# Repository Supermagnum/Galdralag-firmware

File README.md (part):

# Galdr — Galdralag Firmware

## Open Invention Network

This project is **registered with the [Open Invention Network (OIN)](https://openinventionnetwork.com/)**. OIN is a defensive patent pool: members cross-license Linux-related patents so participants can ship and use open-source software with reduced patent exposure.

Status: Waiting for:
https://github.com/betrusted-io/xous-core/pull/937

---

## Table of contents

- [Open Invention Network](#open-invention-network)
- [Security notice: Shamir host split](#security-notice-shamir-host-split-fixed-prior-shares-compromised)
- [What this is](#what-this-is)
  - [Galdra contact metadata](#galdra-contact-metadata)
  - [What this firmware is (and is not)](#what-this-firmware-is-and-is-not)
  - [Signed firmware (Ed25519, boot0)](#signed-firmware-ed25519-boot0)
- [Is this AI slop?](#is-this-ai-slop)
- [Test results](#test-results)
- [Why Rust?](#why-rust)
  - [Memory Safety](#memory-safety)
  - [System-level robustness (with limits)](#system-level-robustness-with-limits)
  - [Key material protection (project patterns)](#key-material-protection-project-patterns)
  - [Auditable by design](#auditable-by-design)
  - [What Rust does not prevent](#what-rust-does-not-prevent)
  - [Setting up a virtual machine for evaluation](#setting-up-a-virtual-machine-for-evaluation)
  - [Risk assessment and deployment](#risk-assessment-and-deployment)
- [Galdralag for dummies](#galdralag-for-dummies)
  - [What is GnuPG?](#what-is-gnupg)
- [GnuPG / OpenPGP keys and Galdra keys](#gnupg--openpgp-keys-and-galdra-keys)
  - [Metadata comparison (GnuPG vs Galdra)](#metadata-comparison-gnupg-vs-galdra)
- [Skipped and ignored tests](#skipped-and-ignored-tests)
- [About the name](#about-the-name)
- [Documentation](#documentation)
- [Code map (function and module index)](docs/CODE_MAP.md)
- [Crate dependencies (upstream vs project)](docs/CRATE_DEPENDENCIES.md)
- [Debugging instructions](docs/DEBUG_INSTRUCTIONS.md)
- [docs/AUDIT_LOG.md](docs/AUDIT_LOG.md)
- [docs/BIOMETRIC_API.md](docs/BIOMETRIC_API.md)
- [docs/HARDWARE_BRINGUP_TEST_PLAN.md](docs/HARDWARE_BRINGUP_TEST_PLAN.md)
- [docs/KEY_LIFECYCLE.md](docs/KEY_LIFECYCLE.md)
- [docs/RRAM_LAYOUT.md](docs/RRAM_LAYOUT.md)
- [docs/THREE_FACTOR_AUTH.md](docs/THREE_FACTOR_AUTH.md)
- [docs/THREAT_MODEL.md](docs/THREAT_MODEL.md)
- [Glossary (plain language)](docs/GLOSSARY.md)
- [OpenPGP and GnuPG compatibility](#openpgp-and-gnupg-compatibility)
- [Token session and key export](#token-session-and-key-export)
- [Web of Trust and Key Signing Parties](#web-of-trust-and-key-signing-parties)
  - [Obtaining your Galdralag fingerprint](#obtaining-your-galdralag-fingerprint)
  - [What is the web of trust?](#what-is-the-web-of-trust)
  - [How it works](#how-it-works)
  - [Key signing parties](#key-signing-parties)
  - [Typical workflow at a key signing party](#typical-workflow-at-a-key-signing-party)
  - [Fingerprints instead of full keys at the event](#fingerprints-instead-of-full-keys-at-the-event)
  - [Keyservers](#keyservers)
  - [Using keyservers](#using-keyservers)
  - [Common keyservers](#common-keyservers)
  - [Best practices and caveats](#best-practices-and-caveats)
  - [Fulla (WoT registry server)](https://github.com/Supermagnum/Fulla)
- [Standards vs. firmware-specific features](#standards-vs-firmware-specific-features)
- [Shamir secret sharing and drive encryption](#shamir-secret-sharing-and-drive-encryption)
- [German eID and Governikus as a trust anchor for public keys](#german-eid-and-governikus-as-a-trust-anchor-for-public-keys)
- [Standards process: Shamir and ephemeral key exchange](#standards-process-shamir-and-ephemeral-key-exchange)
  - [CESS (related open standard)](#cess-related-open-standard)
- [Sequoia PGP (if this repository is unresponsive)](#sequoia-pgp-if-this-repository-is-unresponsive)
- [Platform support (Linux only)](#platform-support-linux-only)
- [Build, install, and uninstall](#build-install-and-uninstall)
  - [Compile firmware](#compile-firmware)
  - [Flashing](#flashing)
  - [Compile and install host tools (`galdra`, `galdrad`, `galdra-gtk`)](#compile-and-install-host-tools-galdra-galdrad-galdra-gtk)
  - [Run `galdrad` and the desktop GUI (`galdra-gtk`)](#run-galdrad-and-the-desktop-gui-galdra-gtk)
  - [Uninstall host tools](#uninstall-host-tools)
- [Key capabilities](#key-capabilities)
  - [What makes this token unusual](#what-makes-this-token-unusual)
  - [Dual-hardware-key quorum (integrator pattern)](#dual-hardware-key-quorum-integrator-pattern)
  - [Cryptographic capabilities](#cryptographic-capabilities)
    - [Asymmetric / key agreement](#asymmetric--key-agreement)
    - [Symmetric / AEAD](#symmetric--aead)
    - [Key derivation / MAC / digest](#key-derivation--mac--digest)
    - [Key management](#key-management)
  - [Security properties](#security-properties)
  - [PIN policy](#pin-policy)
- [Post-quantum status](#post-quantum-status)
  - [Implemented — unaudited crate (feature-gated)](#implemented--unaudited-crate-feature-gated)
  - [Pending independent audit — not yet implemented](#pending-independent-audit--not-yet-implemented)
  - [Will not be implemented](#will-not-be-implemented)
- [Zeroisation — hardware caveat](#zeroisation--hardware-caveat)
- [Workspace layout](#workspace-layout)
- [Cryptographic dependency policy](#cryptographic-dependency-policy)
- [Quick start](#quick-start)
- [Known limitations / open work](#known-limitations--open-work)
  - [CCID initial PIN: Dabao CCID vs legacy CDC](#ccid-initial-pin-dabao-ccid-vs-legacy-cdc)
- [License](#license)

---

## What this is

Firmware for **Baochip-1x** (Dabao evaluation board) devices running the
**[Xous](https://github.com/betrusted-io/xous-core)** microkernel, built
for `riscv32imac-unknown-none-elf`.

It's located here:
https://www.baochip.com/

The device is a hardware security token in the same category as
Nitrokey-class devices, with OpenPGP smartcard-class behaviour and an
encrypted vault. The full hardware stack — RTL, schematics, bootloader,
OS — is open source and auditable.

Hardware specification, boot model, requirement tables, and ComboHash/PKE
usage are documented in **[Supermagnum/Baochip-1x-firmware](https://github.com/Supermagnum/Baochip-1x-firmware)**.
The **Dabao** evaluation board (KiCad, schematics, switches, pinout) is **[baochip/dabao](https://github.com/baochip/dabao)**. To enter **bootloader mode** for flashing, **press SW2** to toggle it (see that repo's schematic).
Architecture notes for this repository: [docs/ARCHITECTURE.md](docs/ARCHITECTURE.md).

### Galdra contact metadata

The **Galdra** host tool keeps a **local SQLite** directory of recipients (contacts). Each stored identity includes public key material plus optional **sidecar labels** (see the table below). These tags live in the host database and, for **Galdra keys**, in the on-chip **contact store** (`crates/contact-store`). They are **not** magically bound to OpenPGP User IDs unless you align them yourself, and they are **not** cryptographically asserted unless you check them **out of band**. Optional **`galdra keyserver push`** can send overlapping fields to a project registry as JSON alongside the exported public key. Per-field provenance on the token uses **SelfAttested**, **HostVerified**, **RegistrySync**, and **OobVerified** (see [Metadata comparison (GnuPG vs Galdra)](#metadata-comparison-gnupg-vs-galdra) and the contact-store layout in [docs/RRAM_LAYOUT.md](docs/RRAM_LAYOUT.md)).

| Field | Purpose | Host (`galdra` SQLite) | On-chip contact store | Format / limit |
|-------|---------|--------------------------|------------------------|----------------|
| **Contact id** | Stable host primary key | Yes | No | Text (`id` in SQLite) |
| **Display name** | Human-readable label | Yes | Yes | UTF-8 string; **240 bytes** max per heap field on chip |
| **E-mail** | Primary mail address | Yes | Yes | UTF-8 string; lookup on chip by e-mail scan |
| **Callsign** | Amateur-radio callsign | Yes | Yes | **12 bytes**, NUL-padded; lookup on chip |
| **DMR subscriber ID** | DMR radio ID | Yes | Yes | **32-bit** unsigned (`0` = absent); lookup on chip |
| **Badge number** | Employee or badge ID | Yes | Yes | UTF-8 string |
| **Organisation** | Agency or employer | Yes | Yes | UTF-8 string |
| **Department** | Team or unit | Yes | Yes | UTF-8 string |
| **Role** | Job or function label | Yes | Yes | UTF-8 string |
| **Note** | Free-form comment | Yes | Yes | UTF-8 string |
| **Radio affiliation** | Club, net, or alliance label | Yes | Yes | UTF-8 string |
| **Street** | Street address line | Yes | Yes | UTF-8 string |
| **Country** | Country name or code | Yes | Yes | UTF-8 string |
| **Postal code** | ZIP or postal code | Yes | Yes | UTF-8 string |
| **Region** | State, county, or region | Yes | Yes | UTF-8 string |
| **Fluxer ID** | Fluxer handle or id | Yes | Yes | UTF-8 string |
| **Discord ID** | Discord user id | Yes | Yes | UTF-8 string |
| **IRC id** | IRC nick or similar | Yes | Yes | UTF-8 string |
| **Phone number** | Voice or SMS contact number | Yes | No | UTF-8 string; **32** characters max on host; submitter-declared, not verified |
| **Fingerprint** | Key anchor (lookup, sync) | Yes (`pgp_fingerprint`) | Yes | **32 bytes**; OpenPGP v4 style on wire; **not** the same as a **`G:`** device fingerprint |
| **Public key** | Encryption / verify material | Yes (`pgp_pubkey`) | Yes (key region) | Algorithm: Ed25519, X25519, Brainpool P-256/P-384/P-512, NIST P-256/P-384, RSA-2048/3072/4096; up to **768 bytes** blob on chip |
| **PIN-protected key** | Key requires PIN unlock | Host stores OpenPGP keys separately | Yes | PIN verifier digest + AES-GCM wrap metadata on chip |
| **Last fetched** | When key material was refreshed | Yes (`fetched_at`) | Yes (`last_fetched`) | UTC on host; **32-bit** timestamp on chip |
| **Expires at** | Key expiry time | Yes | No | UTC datetime in SQLite only |
| **Key source** | How the host record was created | Yes (`source`) | No | e.g. manual, keyserver, WKD, LDAP, file, peer |
| **Field provenance** | Trust label per metadata field | No | Yes (`source_map`) | Two bits per field: SelfAttested, HostVerified, RegistrySync, OobVerified |
| **Record flags** | Active, stale, own-identity, revoked | Partially (host logic) | Yes | e.g. **STALE**, **SELF_KEY** on chip |

Host-side details and CLI behaviour: [docs/GALDRA-TOOL.md](docs/GALDRA-TOOL.md). Wire layout and slot counts: `crates/contact-store/src/layout.rs` and [docs/RRAM_LAYOUT.md](docs/RRAM_LAYOUT.md).

### What this firmware is (and is not)

**This firmware is** a **hardware security token** for **Baochip-1x**: an **OpenPGP card application** over **USB CCID**, with an on-device **vault**, **PIN policy**, and repository-specific features (**cipher profiles** — you can **stack** **up to four** different symmetric ciphers in one cascade, each with its own derived key; see [Key capabilities](#key-capabilities)), Shamir-related flows, authenticated ephemeral ECDH where implemented, and **Galdra** host tools). The primary interoperability target is **GnuPG-style** OpenPGP card usage, not every token protocol on the market.

**This firmware is not:**

- **FIDO2 / CTAP2 / WebAuthn** — different standards; no CTAP **user-presence** button model and no planned CTAP stack. Use a FIDO security key if you need WebAuthn. (See also [OpenPGP and GnuPG compatibility](#openpgp-and-gnupg-compatibility) and the standards table under [Standards vs. firmware-specific features](#standards-vs-firmware-specific-features).)
- **TOTP / HOTP (OATH one-time passwords)** — those protocols expect a **real-time clock** (TOTP) or an OATH-oriented counter workflow and UX; this device is **not** built as a dedicated OTP token.
- **USB HID keyboard "password typer"** — there is no USB keyboard personality to inject keystrokes into the host. Planned credential storage (see [docs/future-todo.md](docs/future-todo.md)) is described as retrieval through **authenticated host tooling**, not HID typing.
- **A general multi-applet Java Card platform** — scope is this **Galdr** firmware and its documented surfaces, not arbitrary third-party smart-card applets.

Crate-level exclusions aligned with the same constraints are listed under **[Crates Explicitly Excluded](docs/future-todo.md#crates-explicitly-excluded)** in [docs/future-todo.md](docs/future-todo.md).

**CESS:** This firmware **conforms to CESS** for the normative constructions implemented in-tree (including **Mode A** outer AEAD, **HKDF-BLAKE3** for **`K_outer`**, and byte-wise GF(2^8) Shamir splitting). The full alignment statement, deviation register, and **certification level** (for example **CESS-CORE** for the full fixed layer) are documented in [docs/CESS_CONFORMANCE.md](docs/CESS_CONFORMANCE.md) and [CESS (related open standard)](#cess-related-open-standard) below.

The **OpenPGP / CCID** application logic is in **`crates/usb-personality`**. On **Xous**, the USB service that exposes CCID is **`usb-bao1x`** (in your **xous-core** checkout), built with feature **`ccid-openpgp`**, using **`crates/baochip-openpgp`** for the OpenPGP RRAM window and provisioning. Layout: [docs/RRAM_LAYOUT.md](docs/RRAM_LAYOUT.md). Pre-production gaps (operator PIN UX, platform map sign-off): [Known limitations / open work](#known-limitations--open-work).

The overall goal remains a complete, tested, open-source hardware security token firmware: **OpenPGP card–style behaviour** for GnuPG over CCID (see [OpenPGP and GnuPG compatibility](#openpgp-and-gnupg-compatibility)), plus **additional on-device features** not currently defined by the OpenPGP card standard — ephemeral ECDH with forward secrecy, Shamir K-of-N, cipher-agnostic profiles, microSD decoy volume — as summarised in [Standards vs. firmware-specific features](#standards-vs-firmware-specific-features). All on open RTL with a reproducible bootloader.

For deployments that need **two separate physical tokens** (or **K-of-N** share-holders) before unlocking servers, firewalls, medicine vaults, or encrypted volumes, see [Dual-hardware-key quorum (integrator pattern)](#dual-hardware-key-quorum-integrator-pattern) under [Key capabilities](#key-capabilities). Each device is **one** credential source; quorum enforcement is **your** access gateway, PAM layer, or panel — not this firmware.

### Signed firmware (Ed25519, boot0)

Shippable firmware for **Baochip-1x** is **signed** with **Ed25519**. You sign the firmware image with an **Ed25519** private key; **GnuPG** can do this with **`gpg --sign`** using an **Ed25519 signing subkey** (the usual OpenPGP detached-signature workflow, adapted to whatever packaging your build emits). The immutable **boot0** ROM in the SoC **verifies** that signature against the **corresponding public keys burned into the device** (and the wider **key manifest** for the boot chain) **before** the next stage — **boot1** — is allowed to run. **boot1** then loads signed application images (for example **UF2** blobs delivered over USB mass storage in bootloader mode). Default parts carry **four** on-chip Ed25519 public keys (roles such as code deployment, beta, and developer); **boot0** / **boot1** enforce a **mutual-distrust** policy between Baochip and third-party signing keys. Full boot flow, **UF2** delivery, console, **boot1** updates, and security model: **[Getting Started with Baochip Targets](https://github.com/betrusted-io/xous-core/blob/dev/README-baochip.md)** in **xous-core**.

## Skipped and ignored tests

Not every test runs in every command; that is intentional.

- **`xtask` not in the default workspace test:** The common recipe is `cargo test --workspace --exclude xtask` because `xtask` is a build-orchestration crate. Run `cargo test -p xtask` when you want its tests.
- **Tests marked `#[ignore]`:** These are skipped unless you pass `--ignored` (and any needed crate filters). Reasons include: coverage that is already exercised in focused unit tests (e.g. post-drop zeroization), **slow** cases (e.g. RSA key generation), and **hardware or token-dependent** flows in host tools such as `galdra` that need a connected device or fixtures.
- **`test-all --no-fuzz`:** Skips the **cargo-fuzz** step to keep CI or quick runs short and to avoid requiring a nightly toolchain for that step; run `cargo run -p xtask -- test-all` without `--no-fuzz`, or invoke fuzz targets separately (see [`fuzz/README.md`](fuzz/README.md)).
- **`test-all --no-dudect`:** Skips the **dudect** timing suite (~15–20 minutes). CI uses this flag (shared runners are too noisy for a hard gate). Run `cargo run -p xtask -- timing-test` or `test-all` without `--no-dudect` locally.
- **Conformance vector suites:** Some groups are not executed (for example certain AES-GCM Wycheproof cases); see [`docs/TEST_RESULTS.md`](docs/TEST_RESULTS.md) for what is in scope.

One can also check integrity of crates with this when the pr is closed:
https://github.com/rust-lang/cargo/issues/16850

> **Status:** Ready for testing by humans, on real hardware — no production-ready release exists.
> It's written in Rust using validated and audited crypto crates. 
> Cryptographic primitives are drawn exclusively from audited workspace
> dependencies. Post-quantum algorithms are feature-gated and marked
> **PENDING INDEPENDENT AUDIT**. See [Post-quantum status](#post-quantum-status).

> **Note:** Parts of this project were developed with AI assistance (Claude, Anthropic).
> The design, cryptographic choices, and security decisions have not been reviewed
> by a professional cryptographer. Treat this as an experimental project and apply
> your own critical judgement. Independent expert review is strongly recommended
> before any production deployment.

It is ready for testing by humans. **You** decide whether to build or run any of this software; there may be bugs that **unit tests, fuzzing, and other checks** have not found. Using an **optional virtual machine** for experimentation **reduces risk** to your host system but does not eliminate it. Detailed results are in **[Test results](#test-results)** ([`docs/TEST_RESULTS.md#run-metadata`](docs/TEST_RESULTS.md#run-metadata)). **Plain-language definitions** (A–Z) of technical terms: **[Glossary](docs/GLOSSARY.md)**.

## Is this AI slop?

The primary developer has a **neurological condition related to dyscalculia**. Dyscalculia affects number sense and related symbolic processing in ways that, for them, make **traditional programming** — hand-authored code editing as the sole workflow — **not workable** without assisted tooling (for example conversational AI editors). That constraint is distinct from correctness: reviewers should still weigh tests, fuzzing, and independent audit as documented elsewhere on this page.

A cryptographer or serious implementer reviewing Galdralag will typically open `crates/vault/tests/` and `crates/cipher-profile/tests/` before reading prose. The test suite is the proof of work: it encodes domain knowledge that cannot be substituted with narrative alone.

That is not a reason to hide the point from everyone else. People evaluating the project for procurement, deciding whether to contribute, or shipping code without deep training in cryptographic testing methodology still deserve a pointer to the concrete evidence. 

**What to look at:** Conformance material includes RFC 8439 worked examples for ChaCha20-Poly1305 under `crates/vault/tests/rfc_vectors/`, vendored Wycheproof JSON for ChaCha20-Poly1305 and Brainpool ECDH/ECDSA edge cases under `crates/vault/tests/data/wycheproof/`, BSI TR-03111 vectors for BrainpoolP256r1 and P384r1 under `crates/vault/tests/bsi_vectors/`, official BLAKE3 reference vectors (all 35 input lengths, all three modes) under `crates/vault/tests/blake3_vectors.json`, Twofish specification vectors (1203 cases including Monte Carlo) under `crates/vault/tests/twofish_vectors.json`, and the project's own CESS cascade KAT fixture with independently verified intermediates under `crates/cipher-profile/tests/fixtures/cascade_cess_kat.json`. Together these are the ground truth the runner and reviewers can exercise with `cargo test --workspace` and `python3 scripts/verify_cascade_kats.py`.

**RFC 8439** is published by the Internet Engineering Task Force (IETF), the organisation that standardises much of how the internet interoperates. RFCs (Request for Comments) are the usual form for protocol and many cryptographic specifications. RFC 8439 defines ChaCha20-Poly1305 authenticated encryption (building on Daniel Bernstein's designs) and includes concrete worked examples with specific inputs and expected outputs so independent implementations can check they match the standard byte-for-byte. The widely reproduced plaintext beginning with *Ladies and Gentlemen of the class of '99: wear sunscreen* appears in the RFC's appendix examples: if your code reproduces the AEAD output exactly, you have a strong check that you implemented the construction correctly. It is the cryptographic analogue of an official answer key. ChaCha20-Poly1305 is the inner layer of every multi-layer cascade profile in this firmware, so this check sits at the foundation of the entire cipher stack.

**Wycheproof** is a test corpus released by Google's security team (2017). The name refers to Mount Wycheproof in Australia — often cited as the world's smallest mountain — because the project focuses on clearing small but fatal hurdles: integer overflows, boundary cases, malformed inputs, and tampered authentication tags; failures that show up repeatedly in real deployed crypto. It complements RFC-style vectors: RFC 8439-style examples demonstrate correctness against the published AEAD; Wycheproof stresses robustness where implementations historically break. In this repository Wycheproof JSON covers ChaCha20-Poly1305, AES-GCM, HMAC, HKDF, X25519, Ed25519, RSA, and Brainpool ECDH/ECDSA variants.

**BSI TR-03111** is the technical guideline for elliptic curve cryptography published by the German Federal Office for Information Security (Bundesamt fur Sicherheit in der Informationstechnik). Version 2.10 is the current revision. The Brainpool curves used in this firmware — P256r1 and P384r1 — are specified in BSI standards, making TR-03111 the natural reference for their test vectors. Each curve has ECDH and ECDSA coverage; ECDSA signatures were additionally cross-checked against an independent Python implementation using the `cryptography` library.

**BLAKE3 reference vectors** are the official test corpus published alongside the BLAKE3 specification by its authors. They cover 35 input lengths from 0 to 102400 bytes, specifically chosen to exercise all internal chunk and tree-hashing boundary conditions that are invisible to short-input tests. All three BLAKE3 modes — default hash, keyed hash, and derive-key — are covered. BLAKE3 is used throughout this firmware for HKDF key derivation and inter-layer integrity checks in the cascade cipher profiles; the boundary coverage matters because BLAKE3's tree construction only activates above 1024 bytes.

**The test suite is also tamper detection for the supply chain.** All cryptographic primitives in this firmware come from audited RustCrypto crates — no cryptography is implemented in-tree. Because the conformance vectors above are run against those crates on every `cargo test --workspace`, any dependency that has been tampered with or substituted will produce a known-answer test failure before the compromised code reaches a deployed system. `python3 scripts/verify_cascade_kats.py` adds a second independent path: a Python implementation checks the same intermediate values in the cascade KAT fixture, so even a compromised Rust toolchain producing wrong output is caught by the cross-check. This is a meaningfully stronger supply chain integrity story than binding to a C library, where equivalent verification of every internal operation requires significantly more effort and specialist tooling.

It is now up to the reader to judge whether these claims are false or not.

## Galdralag for dummies

You plug it into a USB port. From the host's perspective the firmware can present **crypto mode** or **camouflage mode**. In crypto mode your computer sees a smart card: you use **GnuPG** or a compatible OpenPGP stack ([What is GnuPG?](#what-is-gnupg)) the same way you would any other hardware security token — the token handles the sensitive cryptographic operations so your private keys never exist unprotected on your computer. In camouflage mode it can enumerate as ordinary removable storage with innocuous-looking files so a quick look does not reveal its real role; see **Storage camouflage** below.

### What is GnuPG?

**GnuPG** stands for **GNU Privacy Guard**. It is the GNU project's implementation of **OpenPGP**, the open standard for key management and cryptographically protected messages (the same conceptual family as PGP, but specified in documents such as RFC 4880 and community updates). You normally run it as the **`gpg`** command on Linux, BSD, macOS, or Windows; many graphical mail and key utilities wrap this underneath.

People use GnuPG to:

- **Encrypt and decrypt** files or backups so only chosen recipients can read them.
- **Sign data** so others can check authenticity and integrity — common for software releases, distribution mirrors, and personal documents.
- **Protect email** end-to-end when paired with a suitable mail client (GnuPG handles the cryptography; the message format on the wire is OpenPGP).
- **Authenticate**, notably **SSH** logins when **`gpg-agent`** exposes authentication keys from a smart card or local keystore.
- **Lock and unlock an encrypted hard drive.** Linux can scramble a whole drive so it is unreadable without the right key. GnuPG can hold that key on your token, so the drive only opens when the token is plugged in.

**GnuPG and encrypted drives (LUKS).** Linux has a built-in way to encrypt an entire drive or partition, called **LUKS**. Once a drive is encrypted, it looks like meaningless noise to anyone without the key, so a lost or stolen laptop does not hand over your files.

Normally you unlock such a drive by typing a password. GnuPG lets you use your token instead. The idea is simple: the drive's unlock key is itself locked with your token's key. When you want to open the drive, the token unscrambles that unlock key for you, but only while the token is plugged in and you have entered your **PIN**. Pull the token out, and the drive cannot be opened at all, even on the same computer.

In short, this turns the token into a physical key for your encrypted drive. Setting it up (and adding a backup way in, in case the token is ever lost) is done with Linux's own disk tools; the token simply holds the key. If you would rather share the ability to unlock a drive among several people, so that no one person can do it alone, see [Shamir secret sharing and drive encryption](#shamir-secret-sharing-and-drive-encryption).

By default GnuPG stores keys under **`~/.gnupg`**. With an **OpenPGP smart card**, sensitive **private** keys live on the card; **`scdaemon`** (part of the GnuPG suite) talks **CCID**/**USB** to the card while **`gpg`** still assembles OpenPGP packets on the host.

**What you can use it for.** In **crypto mode** the token is meant for the same work as other OpenPGP smart cards: **signing and decrypting** mail and files, **authenticating** (for example SSH when you use `gpg-agent` as usual), and keeping **long-term private keys** off the machine you type on. Organisations can combine that with **Shamir shares** on the token so no single person holds the entire secret (described further below). **GnuPG** is the primary interoperability target on the host: this firmware implements the **OpenPGP card application** over **CCID**, which `scdaemon` drives (`gpg --card-status`, `gpg --card-edit`, and normal encrypt/sign/decrypt with keys on the card). Other software that speaks the same smart-card protocols may work too; commands, slots, algorithms, and current integration limits are in [OpenPGP and GnuPG compatibility](#openpgp-and-gnupg-compatibility). When **NFC** is brought up on the hardware (**planned** integration — **not** in firmware yet), the same device class can support **physical access**: tapping an NFC reader at a **door, gate, or lock panel** can take part in a policy that only releases the lock after cryptographic checks (often combined with PIN, biometrics, or Shamir-style quorum depending on the deployment). The PN532-oriented sketch for readers and panels is in [docs/NFC_PN532_INTEGRATION.md](docs/NFC_PN532_INTEGRATION.md).

That is the short version. Here is what makes it different from other tokens you may have encountered.

**Storage camouflage.** The device can act as ordinary removable storage so its real role is not obvious from a quick look. When you plug it into a typical computer, it can show up like a normal USB drive or SD-backed volume; you can fill the visible filesystem with plausible everyday files (for example vacation photos) so casual browsing reinforces the impression that it is only storage. That frustrates superficial inspection at a desk or checkpoint. Figuring out that it is actually a security token usually means taking the housing apart, not just plugging it in.

**Your keys stay on the device.** When you sign an email or decrypt a file, the private key never leaves the token. The computer sends the data in, the token does the work, the result comes back out. An attacker who compromises your computer gets nothing useful.

**Past sessions stay safe even if the token is stolen.** Most hardware tokens use a long-term private key directly for key agreement. This one generates a fresh throwaway key pair for every session, signs it with the long-term key to prove it is genuine, and then uses the throwaway pair for the actual exchange. If someone steals the token years from now and somehow extracts the long-term key, they still cannot decrypt anything from past sessions. This property is called forward secrecy, and it is unusual in hardware tokens.

**You can split the key between multiple people.** The token can divide the long-term key into N shares so that any K of those shares are needed to reconstruct it — but no single share holder can do anything alone. This is called Shamir secret sharing. It is useful for organisational keys where no single person should have unilateral access, or as a backup strategy where shares are stored in separate locations. This is also unusual in hardware tokens.

**The encryption is layered.** Rather than encrypting your data with a single cipher, the token can run it through multiple independent ciphers in sequence — for example ChaCha20, then Serpent, then Twofish — each using a separately derived key. A future breakthrough that breaks one cipher does not break the others. The specific combination is called a cipher profile, and you can choose from several built-in ones depending on how much caution your situation requires.

My personal recommendation is **BrainpoolP256r1 + ChaCha20-Poly1305 + BLAKE3**. This is the built-in `standard` profile. It uses the BSI Brainpool P-256 curve for ephemeral key agreement, ChaCha20-Poly1305 for symmetric encryption, and BLAKE3 for key derivation and inter-layer integrity. It is fast, well-tested, battery friendly (ChaCha20-Poly1305 was designed to be efficient on hardware without AES acceleration, reducing CPU time and host power draw; P-256 is the smallest of the three Brainpool curves in this firmware), and does not depend on any NIST-designed primitive. If you need a higher margin against a future cryptanalytic break against a single cipher, the `conservative` profile adds a Serpent-256 layer on top.

**The algorithm choices are deliberate.** The ciphers used — ChaCha20-Poly1305, Serpent, Twofish, Camellia — were all designed independently of government standards bodies. AES and the NIST suite are intentionally excluded. This is a conscious choice for users and organisations who want cryptographic independence from any single country's standards process. Camellia was evaluated independently by the EU NESSIE project and Japan's CRYPTREC programme, and is specified in RFC 3713 and ISO/IEC 18033-3.

**A wrong PIN locks you out properly.** The token counts failed PIN attempts before it checks whether the PIN is correct, not after. This means a crash or power loss mid-attempt cannot be exploited to reset the counter. After too many wrong attempts the token zeroises sensitive material.

**What it does not do yet.** There is no hardware available yet — this is firmware under active development. End-to-end testing with real USB hardware and GnuPG is a future milestone. **NFC** transport and **door-style access readers** are described in the documentation as **integration targets**, not shipped behaviour yet. The biometric third factor described in the documentation is not yet implemented. Some timing side-channel tests that require real hardware cannot be completed until a device exists.

---

## GnuPG / OpenPGP keys and Galdra keys

Galdralag can work with two different kinds of asymmetric key at once. They answer different questions on the device and on the host, and they are not interchangeable even when they belong to the same person. The sections **OpenPGP and GnuPG compatibility**, **Web of Trust and Key Signing Parties**, [Galdra contact metadata](#galdra-contact-metadata), and [Metadata comparison (GnuPG vs Galdra)](#metadata-comparison-gnupg-vs-galdra) describe each stack in more detail; here is how they differ in everyday terms.

An **OpenPGP key**, in the sense GnuPG generates and uses, is a structured packet, not a bare public number. It bundles the primary key, subkeys for signing and encryption, and one or more **User IDs** — usually a display name and an email address such as `Alice Example <alice@example.org>`. Other people can sign those User IDs to say they believe the identity claim is genuine; that social graph is the basis of the web of trust described in **Web of Trust and Key Signing Parties** later in this README. When Galdralag acts as an OpenPGP smartcard, it holds the **private** key material on chip and performs signing and decryption there. The **public** key, the User IDs, and the signatures from others live on the host and are managed by GnuPG in the usual way. The token does not change the OpenPGP message format on the wire; GnuPG treats it like any other OpenPGP card.

A **Galdra key** is a bare asymmetric keypair — Ed25519, X25519, or one of the Brainpool or NIST curves the firmware supports. The key bytes themselves carry **no** identity claims: no User ID packets, no email baked in, no web-of-trust signatures attached to the key structure. Identity for a Galdra key comes from the **contact record** stored next to it in the host SQLite database and the on-chip **contact store**, tied to the key by its fingerprint.

### Metadata comparison (GnuPG vs Galdra)

The table below compares **identity and contact metadata** field by field. **OpenPGP / GnuPG** columns describe what you get from a normal certificate and User ID (plus optional host-side contact rows in **Galdra** when you store an OpenPGP public key in the same directory). **Galdra key** columns describe structured sidecar fields for operational contacts (full host and on-chip detail in [Galdra contact metadata](#galdra-contact-metadata)). A dash means that stack has no standard, separate field for that item.

| Metadata field | OpenPGP / GnuPG | Galdra key (host + contact store) |
|----------------|-----------------|-----------------------------------|
| **Contact / record id** | No (use key ID or fingerprint) | Yes (SQLite `id` on host; not on chip) |
| **Display name** | Only inside **User ID** text (`Name <email>`) | Yes (separate UTF-8 field) |
| **E-mail** | Only inside **User ID** text | Yes (separate field; lookup by e-mail on chip) |
| **Street address** | No standard field | Yes |
| **Country** | No standard field | Yes |
| **Postal / ZIP code** | No standard field | Yes |
| **Region / state** | No standard field | Yes |
| **Organisation** | No standard field | Yes |
| **Department** | No standard field | Yes |
| **Role / job title** | No standard field | Yes |
| **Badge / employee id** | No standard field | Yes |
| **Callsign** | No standard field | Yes (**12** bytes, NUL-padded on chip) |
| **DMR subscriber ID** | No standard field | Yes (**32-bit**; lookup on chip) |
| **Radio affiliation** | No standard field | Yes |
| **Fluxer ID** | No standard field | Yes |
| **Discord ID** | No standard field | Yes |
| **IRC id** | No standard field | Yes |
| **Phone number** | No standard field | Yes (host SQLite only) |
| **Free-form note** | No standard field | Yes |
| **OpenPGP v4 fingerprint** | Yes (**40** hex chars) | Optional on host row when linking a cert (`pgp_fingerprint`); **32** bytes on chip for Galdra keys |
| **`G:` device fingerprint** | No | Yes (BLAKE3-160 over SIG public key; host tool; **not** the OpenPGP v4 value) |
| **OpenPGP key ID** | Yes (short / long form) | No |
| **Trust / provenance** | **WoT** signatures on User IDs | Per-field labels: SelfAttested, HostVerified, RegistrySync, OobVerified (on chip) |
| **Key expiry** | Yes (certificate / subkey) | Host only (`expires_at` in SQLite) |
| **Last key fetch time** | Host tooling dependent | Yes (`fetched_at` / `last_fetched`) |
| **Private key on token** | **SIG**, **DEC**, **AUT** card slots | Separate **Galdra** key region (not User ID packets) |
| **PIN to use private key** | PW1 / PW3 (OpenPGP card) | Optional PIN wrap per Galdra contact record |

OpenPGP puts **name and e-mail in one User ID string**; it does not give you separate, machine-readable callsign, DMR, or postal fields. **Galdra** keeps those as named columns so radio and operations teams can search and display them without parsing certificate text.

| OpenPGP card object (not in table above) | Host (GnuPG) | On token |
|------------------------------------------|--------------|----------|
| Primary + **SIG** / **DEC** / **AUT** subkeys | Public in keyring | Private in sealed slots |
| **Certification signatures** (WoT) | Yes | No |
| **Revocation certificate** | Yes | No |
| **Algorithm attributes** (DO **0xC1** / **0xC2** / **0xC3**) | `gpg --card-edit` | Yes |

Tokens upgraded from firmware that offered BrainpoolP512r1 may still return P-512 attributes on GET DATA; GnuPG operations on those slots then fail with generic card errors. Run `galdra device status` (or see [docs/OPENPGP_CARD.md](docs/OPENPGP_CARD.md)) to identify stale slots; removal background is in [CHANGELOG.md](CHANGELOG.md).
| **PW1** / **PW3** | Never stored | Verifier on chip (min **5** chars, **3** tries default) |
| **Cardholder DOs** (login, language, URL, …) | Cached by GnuPG | Optional (**254** bytes max per DO) |

Card application **3.4.1**, CCID, and GnuPG workflows: [docs/OPENPGP_CARD.md](docs/OPENPGP_CARD.md) and [OpenPGP and GnuPG compatibility](#openpgp-and-gnupg-compatibility).

The split exists because the identity information that matters in the communities Galdralag targets — callsign, DMR ID, radio network affiliation — has no natural home in an OpenPGP User ID. A User ID is meant for name and email. Writing something like `LA5XYZ <la5xyz@example.org> DMR:2345678` into a User ID string is informal, unstructured, and not machine-readable in any standard way. Galdra keys keep the cryptographic material clean and put operational identity in a record format the host tool and on-chip store understand natively.

In practice, a single device can hold **both** kinds of key without conflict. The OpenPGP card application serves GnuPG through the standard SIG, DEC, and AUT slots. The contact store holds Galdra keys for operational work — for example encrypting to a radio contact by callsign, checking a message against a DMR subscriber ID, or looking up a colleague by badge number. The two paths do not step on each other.

If someone has an OpenPGP certificate managed by GnuPG on the host **and** a Galdra key in the on-chip contact store, those are **two separate keys** with **two separate fingerprints**. The Galdra fingerprint — prefixed `G:` and derived with BLAKE3 from the raw public key bytes — is **not** the same value as the OpenPGP v4 fingerprint of that person's GnuPG certificate. The host tool and the device treat them as independent identities. Do not assume one fingerprint implies the other without checking both.

Neither key type automatically vouches for the labels around it. An OpenPGP User ID is self-asserted until someone else signs it. A callsign or DMR field in a Galdra contact record is only as trustworthy as its source — a keyserver fetch, a manual entry, or an out-of-band check you performed yourself. The provenance labels (SelfAttested, HostVerified, RegistrySync, OobVerified) record **how** a field arrived; they do not replace the work of actually verifying the identity you care about.

---

## Why Rust?

This firmware is written in Rust, a systems programming language designed
to be as fast and low-level as C or C++, but with a fundamentally different
approach to safety.

Every dependency is classified as **unchanged upstream** (crates.io as published),
**altered or vendored in-tree** (pinned copy or workspace patch), or **created by this
project** (firmware, host, and tooling crates). The full inventory, roles, and
dependency graph are in **[docs/CRATE_DEPENDENCIES.md](docs/CRATE_DEPENDENCIES.md)**.

### Memory Safety

A large share of security-relevant bugs in industry codebases come from **memory unsafety** (buffer overflows, use-after-free, null dereferences, and similar). Microsoft's MSRC has **repeatedly reported** that roughly **70% of CVEs addressed in their own products** fall into this category; the **Chrome** team has published similar proportions for Chrome. Those figures describe **those vendors' products**, not a universal law for all firmware, but they illustrate why memory-safe languages matter.

In **safe Rust** (the default), the **borrow checker** rules out data races and the usual undefined-behaviour memory errors at compile time **without** relying on garbage collection. **Unsafe Rust** and **FFI** to C can still introduce memory bugs; they must be kept small and reviewed.

### System-level robustness (with limits)

Rust's **bounds checking** on slices and its **ownership rules** reduce several classes of failure modes common in C/C++ embedded code:

- **Buffer and stack smashes** that corrupt control flow are caught at compile time in safe code or via checked indexing at runtime instead of silent UB.
- **Data races** in concurrent safe Rust are rejected by the compiler (deadlocks are **not** eliminated — see below).
- **`unsafe` blocks** must be explicit; **MMIO** and raw pointers for registers live there, so reviewers can **grep** for the audit surface (unsafe does **not** make incorrect MMIO impossible, only easier to localize).

Rust does **not** by itself stop **logic bugs** such as a tight loop that wears **flash**, or choosing wrong register values. Those remain engineering and review concerns.

### Key material protection (project patterns)

This codebase applies common Rust patterns for secrets; they are **not** automatic for every type:

- Types like **`zeroize::Zeroize` / `ZeroizeOnDrop`** clear buffers on drop; callers opt in.
- **Secret comparisons** use **`subtle::ConstantTimeEq`** (and similar) where timing matters — ordinary `==` is not magically constant-time.
- **No `Copy` on secret wrappers** reduces accidental duplication; domain separation uses **distinct types** and **HKDF labels** ([Cryptographic dependency policy](#cryptographic-dependency-policy)).
- **Panic behaviour** and **drop order** follow Rust rules; use `catch_unwind` or `abort` strategies where your platform requires stronger guarantees.

### Auditable by design

**`unsafe`** must be **spelled out** in source, which narrows manual review. **Dependencies:** this project's cryptographic policy favours **audited Rust crates** (RustCrypto and others); see the table in [Cryptographic dependency policy](#cryptographic-dependency-policy) — not every dependency is from a single umbrella project. For the complete crate list and whether each dependency is unchanged, altered/vendored, or project-authored, see **[docs/CRATE_DEPENDENCIES.md](docs/CRATE_DEPENDENCIES.md)**.

### What Rust does not prevent

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
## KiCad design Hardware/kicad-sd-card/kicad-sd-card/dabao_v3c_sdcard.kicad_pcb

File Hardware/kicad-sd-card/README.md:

# Dabao board design files (SD card)

This directory contains the KiCad design files for the Dabao USB-A security token with the Baochip-1x. This revision adds a micro-SD card holder (`dabao_v3c_sdcard` project).

**Outputs and previews**

- [dabao_v3c_sdcard.pdf](dabao_v3c_sdcard.pdf) — schematic / design PDF export  
- [dabao_v3c_sdcard.jpg](dabao_v3c_sdcard.jpg) — top of the PCB (render or photo)  
- [dabao_v3c_sdcard-b.jpg](dabao_v3c_sdcard-b.jpg) — bottom of the PCB

**Enclosure — FreeCAD source**

- [Enclosure/Enclosure.FCStd](Enclosure/Enclosure.FCStd) — FreeCAD project file (`.FCStd`). Open it in [FreeCAD](https://www.freecad.org/), a free, open-source parametric 3D modeler for Windows, macOS, and Linux.

**Enclosure — STL for 3D printing**

- [Enclosure/stl-files/](Enclosure/stl-files/) — STL (STereoLithography) triangle meshes exported from the enclosure CAD. Use these files with a slicer for FDM or resin printing; they include the top and bottom shell, PCB reference solid, and screw part meshes.

**Enclosure — STEP (STP) for CAD**

- [Enclosure/stp-files/](Enclosure/stp-files/) — STEP / STP files (ISO 10303) exported from the enclosure model. These are precise solid models for import into CAD or CAM tools (machining, further editing, or mesh conversion), including body assemblies and screw parts.

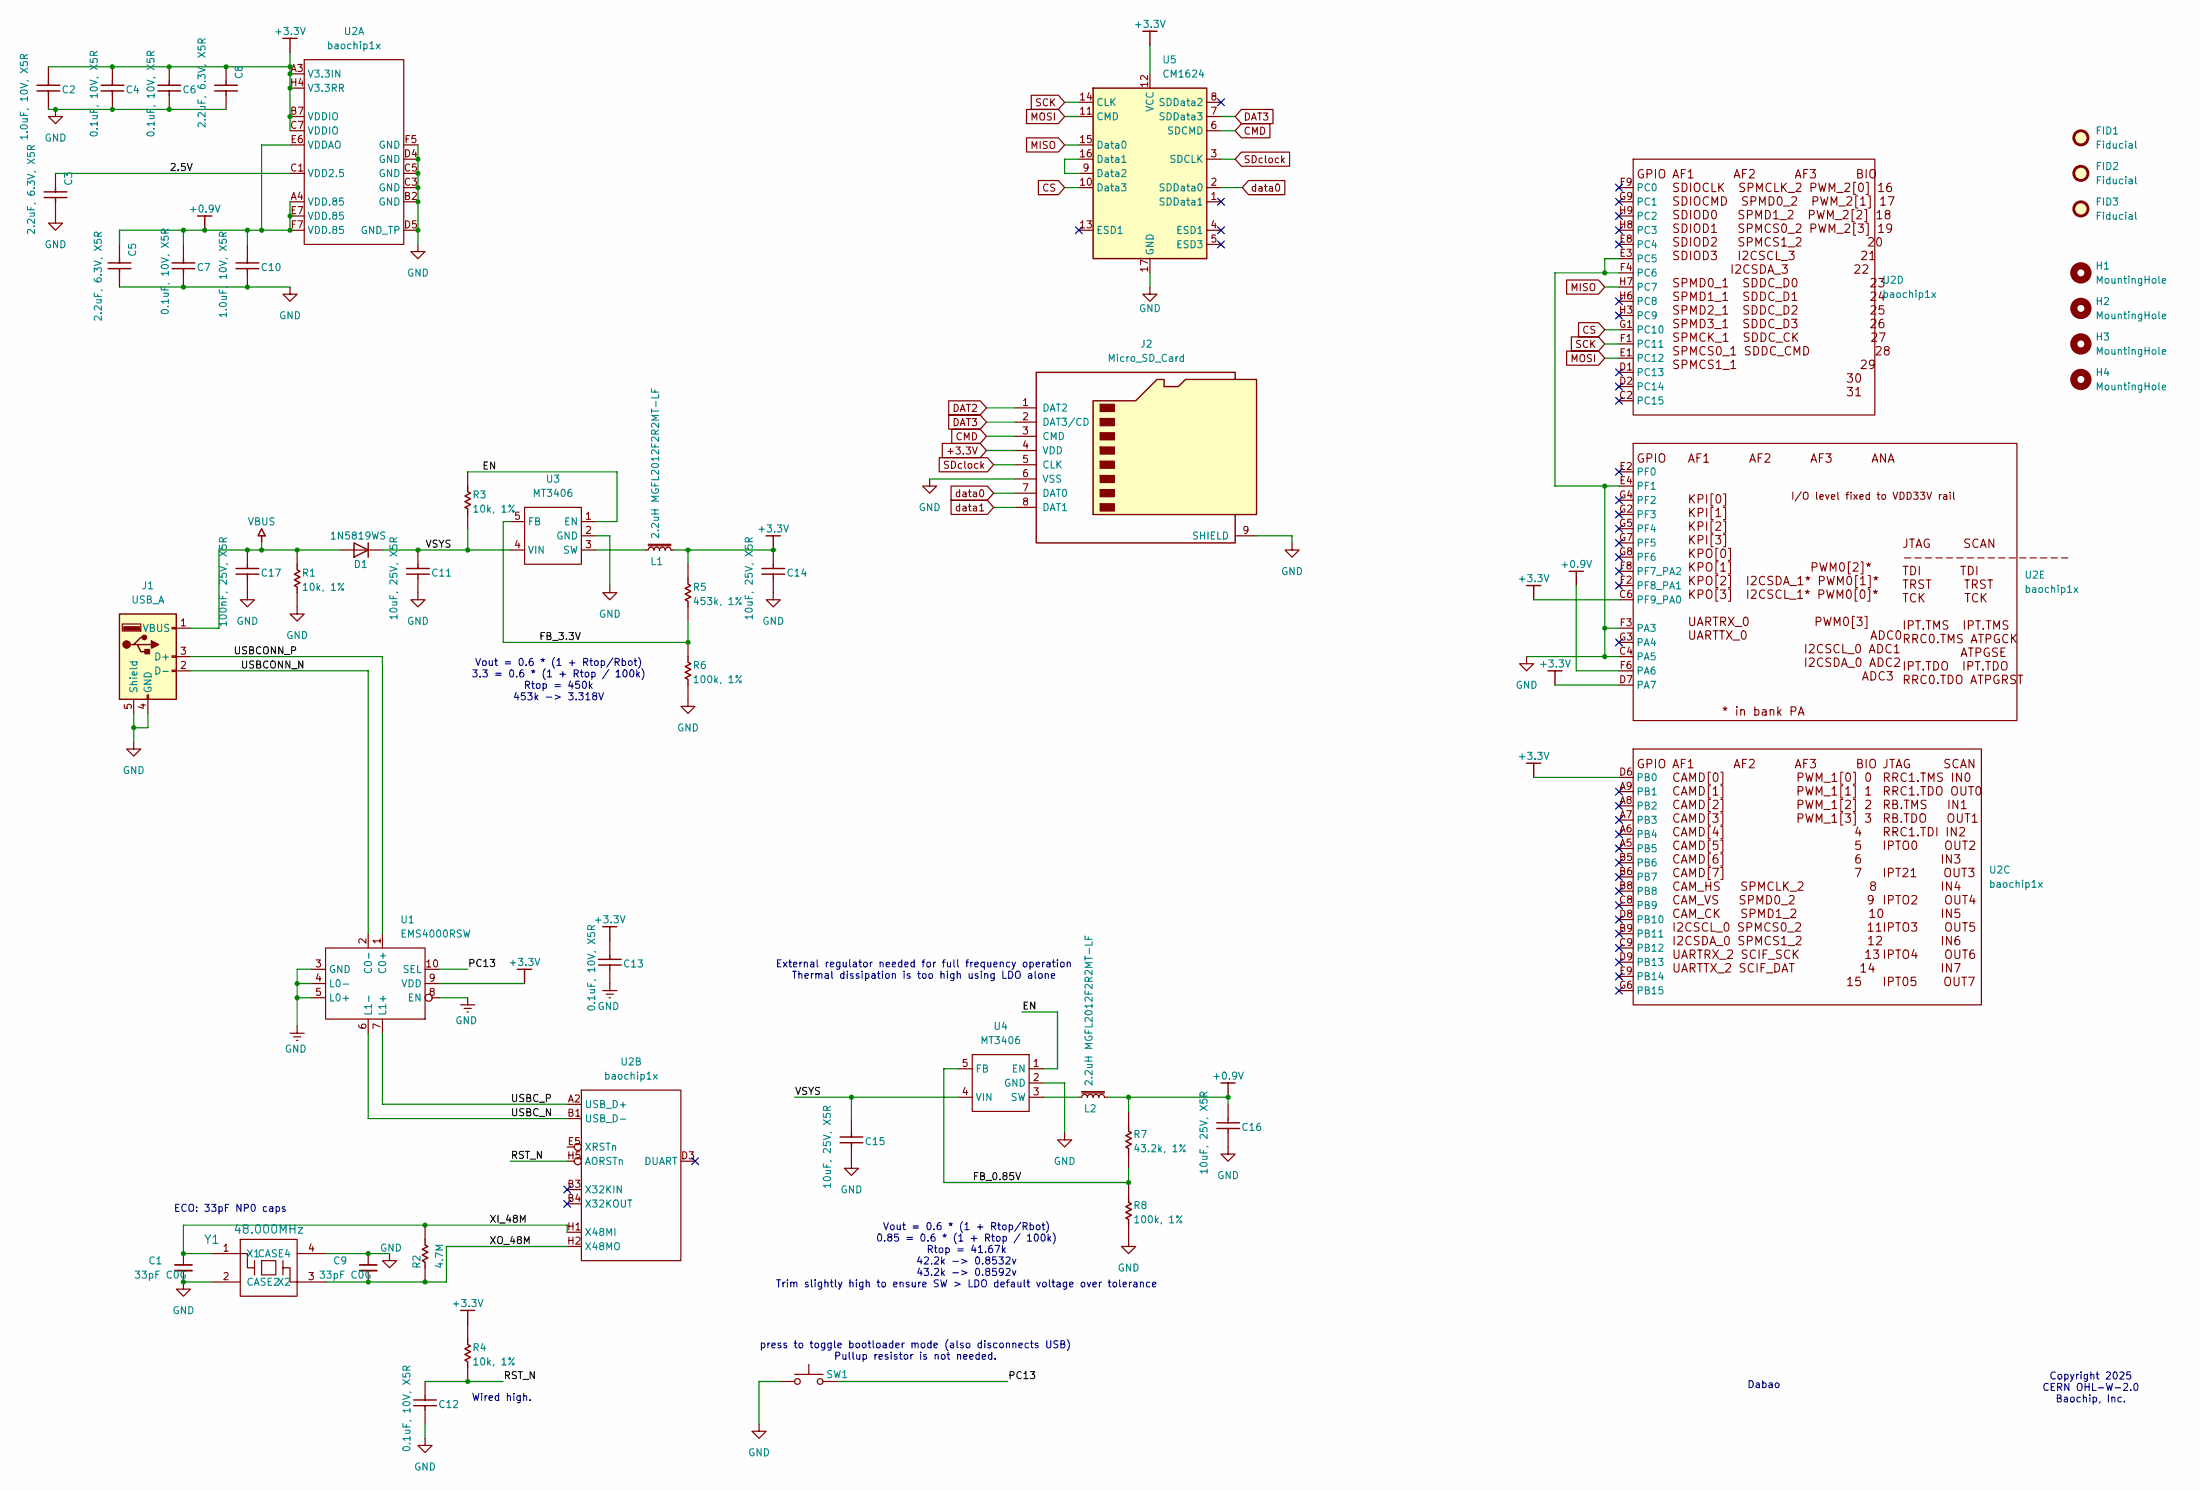
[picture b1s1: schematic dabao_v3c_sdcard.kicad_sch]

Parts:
C1, C9: 33pF C0G; C_0201_0603Metric; LCSC C56903
C2, C10: 1.0uF, 10V, X5R; C_0201_0603Metric; MPN CL05A105KA5NQNC; LCSC C76935
C3, C5, C8: 2.2uF, 6.3V, X5R; C_0201_0603Metric; MPN GRM033R60J225ME47D; LCSC C76933
C4, C6, C7, C12, C13: 0.1uF, 10V, X5R; C_0201_0603Metric; MPN CL05B104KO5NNNC; LCSC C76934
C11, C14, C15, C16: 10uF, 25V, X5R; C_0603_1608Metric; MPN CL10A106MA8NRNC; LCSC C96446
C17: 100nF, 25V, X5R; C_0603_1608Metric; MPN CC0603KRX5R8BB104
D1: 1N5819WS; D_SOD-323; MPN SD103AWS; LCSC C191023
FID1, FID2: Fiducial; IRIS fiducial 0.4mm
FID3: Fiducial; IRIS fiducial2 0.4mm
H1, H2, H3, H4: MountingHole; MountingHole_2.2mm_M2_DIN965
J1: USB_A; USB_A_CNCTech_1001-011-01101_Horizontal
J2: Micro_SD_Card; microSD_HC_Hirose_DM3AT-SF-PEJM5
L1, L2: 2.2uH MGFL2012F2R2MT-LF; L_0805_2012Metric; LCSC C281115
R1, R3, R4: 10k, 1%; R_0201_0603Metric; MPN ANY; LCSC C106225
R2: 4.7M; R_0402_1005Metric; MPN ANY; LCSC C474132
R5: 453k, 1%; R_0201_0603Metric; MPN ANY; LCSC C423509
R6, R8: 100k, 1%; R_0201_0603Metric; MPN ANY; LCSC C106224
R7: 43.2k, 1%; R_0201_0603Metric; MPN ANY; LCSC C158519
SW1: SW_Push; SW_Push_1P1T_XKB_TS-1187A; MPN TS-1187A-B-B-B; LCSC C528026
U1: EMS4000RSW; QFN-10_1.4x1.8_Pitch0.4mm; LCSC C49186227
U2: baochip1x; WLCSP-71_9x8_4.062x3.762mm
U3, U4: MT3406; SOT-23-5; LCSC C22462728
U5: CM1624; OnSemi_UDFN-16-1EP_1.35x3.3mm_P0.4mm_EP0.4x2.8mm
Y1: 48.000MHz; Crystal_SMD_3225-4Pin_3.2x2.5mm; LCSC C2892060

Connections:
+0.9V: C5.1, C7.1, C10.1, C16.1, L2.2, R7.1, U2.A4 (VDD.85), U2.E6 (VDDAO), U2.E7 (VDD.85), U2.F6 (PA6), U2.F7 (VDD.85)
+3.3V: C2.1, C4.1, C6.1, C8.1, C13.1, C14.1, J2.4 (VDD), L1.2, R4.1, R5.1, U1.9 (VDD), U2.A3 (V3.3IN), U2.B7 (VDDIO), U2.C6 (PF9_PA0), U2.C7 (VDDIO), U2.D6 (PB0), U2.D7 (PA7), U2.H4 (V3.3RR), U5.12 (VCC)
/2.5V: C3.1, U2.C1 (VDD2.5)
/EN: R3.1, U3.1 (EN), U4.1 (EN)
/FB_0.85V: R7.2, R8.1, U4.5 (FB)
/FB_3.3V: R5.2, R6.1, U3.5 (FB)
/PC13: SW1.2, U1.10 (SEL)
/RST_N: C12.1, R4.2, U2.H5 (AORSTn)
/USBCONN_N: J1.2 (D-), U1.2 (C0-)
/USBCONN_P: J1.3 (D+), U1.1 (C0+)
/USBC_N: U1.6 (L1-), U2.B1 (USB_D-)
/USBC_P: U1.7 (L1+), U2.A2 (USB_D+)
/VSYS: C11.1, C15.1, D1.1 (K), R3.2, U3.4 (VIN), U4.4 (VIN)
/XI_48M: C1.1, R2.2, U2.H1 (X48MI), Y1.1 (X1)
/XO_48M: C9.2, R2.1, U2.H2 (X48MO), Y1.3 (X2)
CMD: J2.3 (CMD), U5.6 (SDCMD)
CS: U2.G1 (PC10), U5.10 (Data3)
DAT2: J2.1 (DAT2)
DAT3: J2.2 (DAT3/CD), U5.7 (SDData3)
GND: C1.2, C2.2, C3.2, C4.2, C5.2, C6.2, C7.2, C8.2, C9.1, C10.2, C11.2, C12.2, C13.2, C14.2, C15.2, C16.2, C17.2, J1.4 (GND), J1.5 (Shield), J2.6 (VSS), J2.9 (SHIELD), R1.2, R6.2, R8.2, SW1.1, U1.3 (GND), U1.4 (L0-), U1.5 (L0+), U1.8 (EN), U2.B2 (GND), U2.C3 (GND), U2.C4 (PA5), U2.C5 (GND), U2.D4 (GND), U2.D5 (GND_TP), U2.E3 (PC5), U2.E4 (PF1), U2.F3 (PA3), U2.F4 (PC6), U2.F5 (GND), U3.2 (GND), U4.2 (GND), U5.17 (GND), Y1.2 (CASE2), Y1.4 (CASE4)
MISO: U2.H7 (PC7), U5.15 (Data0)
MOSI: U2.E1 (PC12), U5.11 (CMD)
unnamed: L1.1, U3.3 (SW)
unnamed: L2.1, U4.3 (SW)
unnamed: U5.9 (Data2), U5.16 (Data1)
SCK: U2.F1 (PC11), U5.14 (CLK)
SDclock: J2.5 (CLK), U5.3 (SDCLK)
VBUS: C17.1, D1.2 (A), J1.1 (VBUS), R1.1
data0: J2.7 (DAT0), U5.2 (SDData0)
data1: J2.8 (DAT1)

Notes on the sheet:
Vout = 0.6 * (1 + Rtop/Rbot) 3.3 = 0.6 * (1 + Rtop / 100k) Rtop = 450k 453k -> 3.318V
External regulator needed for full frequency operation Thermal dissipation is too high using LDO alone
Copyright 2025 CERN OHL-W-2.0 Baochip, Inc.
Dabao
ECO: 33pF NP0 caps
press to toggle bootloader mode (also disconnects USB) Pullup resistor is not needed.
Vout = 0.6 * (1 + Rtop/Rbot) 0.85 = 0.6 * (1 + Rtop / 100k) Rtop = 41.67k 42.2k -> 0.8532v 43.2k -> 0.8592v Trim slightly high to ensure SW > LDO default voltage over tolerance
Wired high.

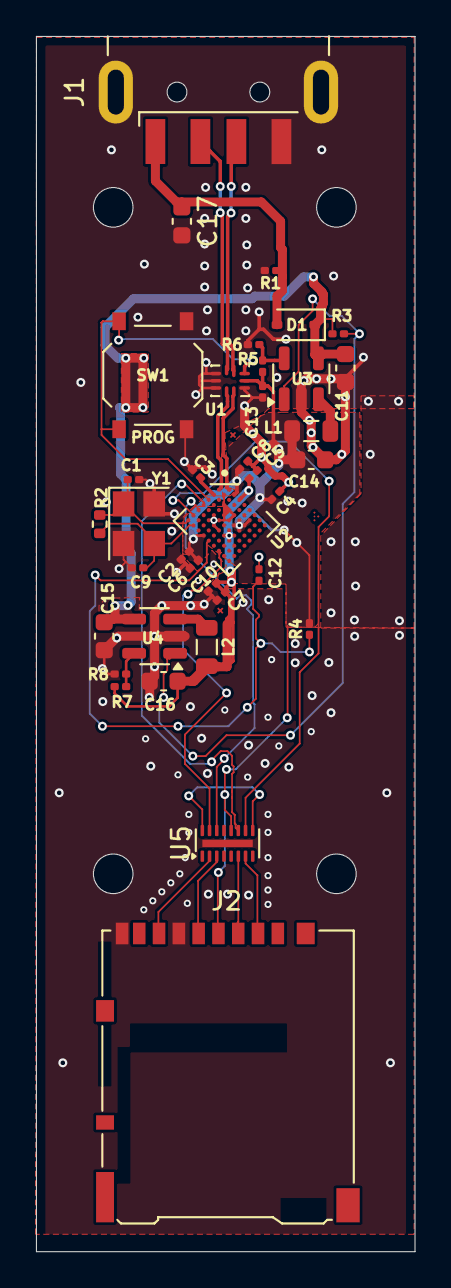
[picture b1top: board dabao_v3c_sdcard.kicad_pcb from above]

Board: 2 copper layers, 21.0 x 67.5 mm, 44 parts (0 on the bottom side), 28 nets.

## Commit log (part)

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2026-03-25 Add Galdr Cargo workspace scaffold and documentation
    Introduce galdr-core, vault, pin-policy, usb-personality, host-tools, and
    xtask for Baochip-1x / Xous firmware bring-up. Include HAL traits with
    test-hal fakes, architecture doc, RFC-oriented crypto dependency tests in
    galdr-core, and README with etymology and project links.
    Made-with: Cursor
2026-03-25 README: clarify runes as shamanic usage for those who understand
    Made-with: Cursor
2026-03-26 Add AI disclaimer to README
    Clarify that AI-assisted content requires human review and is not a
    substitute for security analysis or audit.
    Made-with: Cursor
2026-03-26 Add crypto vault stack, integration tests, xtask test-all, and docs
    - bp512, vault (Brainpool, RSA, Shamir, vectors), pin-policy, security-tests
    - galdr-core: HAL, RFC tests, zeroise simulation; vendored subtle patch
    - xtask: test-all with optional --no-fuzz; fuzz targets (corpus gitignored)
    - Documentation: GALDRA-TOOL, test results, hardware verification, PQ notes
    - README: flashing instructions for riscv32imac; link Baochip upstream README
    - Cargo.lock and .gitignore (target/, fuzz corpus and artifacts)
2026-03-26 Add dudect timing harnesses, extend Wycheproof coverage, refresh test docs
    - security-tests: dudect_stats, dudect_harnesses, dudect_galdr binary; stderr
    progress before each harness; summary and exit message on completion
    - vault: additional Wycheproof JSON runners and test data (AES-GCM, HMAC,
    HKDF, X25519, Ed25519, Brainpool P256 ECDH/ECDSA)
    - xtask: timing-test runs dudect_galdr; test-all invokes timing harness
    - docs: TEST_RESULTS.md Wycheproof section with 18/18 pass table; README
2026-03-26 dudect: sample counts, RSA OAEP bench fix, README and TEST_RESULTS
    - Print measured total_timings; Brainpool P256/P384 at 5k, P512 at 15k
    - RSA OAEP/PSS: align OAEP flip with PSS, prebuild work, drop Arc in loop
    - Document timing-test in README capability table; refresh TEST_RESULTS dudect section
    Made-with: Cursor
2026-03-26 Docs: prominent GALDRA-TOOL link, build/install, keys/Shamir guide
    - README: link to docs/GALDRA-TOOL.md under title and in TOC; build/install/
    uninstall; status text; TEST_RESULTS and supply-chain notes as applicable
    - GALDRA-TOOL: operational guide (keys, Shamir), build/install pointer, TOC
    Made-with: Cursor
2026-03-26 README: rename TOC entry to Galdra tool usage and specifications
    Made-with: Cursor
2026-03-26 README: recommend testing and debugging in a Linux VM
    Isolated VM reduces risk when exercising builds, host tools, and USB flows;
    automation does not eliminate bugs.
    Made-with: Cursor
2026-03-26 README: put About the name first in table of contents
    Made-with: Cursor
2026-03-26 dudect: PBKDF2 at 100k samples; docs for GaldrError/HKDF; refresh TEST_RESULTS
    - Reduce DUDECT_SAMPLES_PBKDF2 to match default harness count (faster timing-test).
    - Rustdoc GaldrError/HalError and derive_subkey_sha512 parameters/errors.
    - Update docs/TEST_RESULTS.md and README dudect figures from latest timing-test (~910s).
    Made-with: Cursor
2026-03-27 docs: expand GLOSSARY (ComboHash, PKE, Sequoia, SQLCipher, age); README links
    - Add galdra-core-host and GALDRA-TOOL cross-refs.
    - README: glossary in TOC, ECDHE subsection in primitives TOC, dev-ref link.
    Made-with: Cursor
2026-03-27 docs: TOC + callout for Serpent/ChaCha/ECDHE/Shamir profile example
    Made-with: Cursor
2026-03-27 docs: AI assistance note, VM testing, and review disclaimer in README
    Made-with: Cursor
2026-06-18 docs: add README table of contents
    Made-with: Cursor
2026-06-18 Update README.md
    Codebase has been fuzzed.
2026-06-18 README: Sequoia PGP path when upstream is unresponsive
    Add TOC entry and subsection with sequoia-pgp.org contribute/docs/contact,
    GitLab/GitHub, and IETF coordination for new ciphers and standards work.
    Made-with: Cursor
2026-06-18 README: map OpenPGP/GnuPG standards vs firmware-specific features
    Add Standards vs firmware-specific section with table (card, CCID, RFC 4880,
    Shamir, ephemeral ECDH, profiles, PSRAM, FIDO2). Clarify What this is and
    OpenPGP card vs message format; link unusual capabilities to that split.
    Made-with: Cursor
2026-06-18 Document OpenPGP and GnuPG compatibility in README
    Add TOC entry, Documentation link to OPENPGP_CARD.md, dedicated section on
    CCID/GnuPG host model, key slots, out-of-scope FIDO2, and Xous USB status.
    Made-with: Cursor
2026-06-18 Add OpenPGP/CCID stack, vault sealed keys, openpgp_dispatch fuzz target
    - usb-personality: CCID framing, OpenPGP APDU dispatch and vault backend, tests
    - vault: sealed key layout and KDF policy hooks
    - fuzz: openpgp_dispatch harness; document in README and TEST_RESULTS (12-target matrix, long run)
    - services/galdralag stub, xtask updates, Psram/dev-ref and OpenPGP integration docs
    Made-with: Cursor
2026-06-18 docs(readme): link Hardware folder for USB dongle design; gitignore local-only drafts
    Made-with: Cursor
2026-06-18 docs: API reference annex, NFC/PN532, SDMMC, usb-pcb; README index
    - Add API_REFERENCE (Shamir, ephemeral session annex for IETF implementors)
    - Add NFC_PN532_INTEGRATION and SDMMC_STORAGE_INTEGRATION
    - Refine usb-pcb (KiCad, FreeCAD, USB-A power vs USB-C PD)
    - Psram: link SD alternative; README table lists all docs + usb-pcb blurb
    Made-with: Cursor
2026-06-18 README: add Why Rust section (memory safety, audit surface, limits)
    Include TOC entries; fix status line It's/Rust capitalization.
    Made-with: Cursor
2026-06-18 docs(readme): move table of contents below status and intro
    Made-with: Cursor
2026-06-18 docs: rename usb-pcb.md to USB_DONGLE_PCB.md, clarify Pico eval vs dongle
    Made-with: Cursor
2026-06-18 chore(hardware): track FreeCAD enclosure; ignore FCBak backups
    Made-with: Cursor
2026-06-18 docs(hardware): add README with dabao PDF and board image
    Made-with: Cursor
2026-06-18 Add files via upload
    added missing files
2026-06-18 chore(hardware): use Enclosure.FCStd as canonical FreeCAD document
    Made-with: Cursor
2026-06-18 Clarify README for Dabao board design files
    Updated description to specify USB-A version and security token.
2026-06-18 chore(hardware): add enclosure STEP exports
    Made-with: Cursor
2026-06-18 chore(hardware): remove enclosure blueprint PDFs
    Made-with: Cursor
2026-06-18 chore(hardware): rename enclosure blueprints to .pdf
    Made-with: Cursor
2026-06-18 chore(hardware): update Enclosure FreeCAD project
    Made-with: Cursor
2026-06-18 docs(readme): reference CESS standard and repository
    Made-with: Cursor
2026-06-18 chore(hardware): update enclosure FreeCAD and bottom STL
    Made-with: Cursor
2026-06-18 chore(hardware): refresh enclosure FreeCAD and bottom shell exports
    Made-with: Cursor
2026-06-18 README: token session, key export policy, public key import
    Document unplug/session/PIN behaviour, public-only export across USB,
    on-device public-key import via vault slots (public_key_vault).
    Made-with: Cursor
2026-06-18 Add CESS crate, Mode A host integration, and conformance documentation
    Introduce the cess workspace crate (HKDF-BLAKE3, Mode A ChaCha outer, wire layout)
    and ephemeral-session K_outer derivation. Wire optional CESS Mode A wrapping into
    galdra and galdrad encrypt/decrypt paths. Document CESS alignment in
    docs/CESS_CONFORMANCE.md and update README for conformance claims and standards
    section edits.
    Made-with: Cursor
2026-06-18 Fix typo in README regarding microSD card
2026-06-18 docs: plain-language glossary (A–Z) and README links
    Rewrite GLOSSARY.md for non-technical readers; keep alphabetical sections.
    Link from intro, TOC, Documentation header, and docs table.
    Made-with: Cursor
2026-06-18 Restructure TEST_RESULTS: run metadata table, sections 1–8
    - Replace TOML block with Run metadata table; horizontal rules around pipeline
    - Renumber sections (crypto 2.1–2.4, dudect 3, key lifecycle 4, OpenPGP 5,
    cargo-fuzz 6 with bash snippets, zeroisation+PIN 7, not automated 8)
    - xtask test-all build_markdown emits the new layout; README links use #run-metadata
    - Fix KAT/twofish asset paths in 2.4; align dudect notes and not-yet-wired block
    Made-with: Cursor
2026-06-18 Hardware: move KiCad project into kicad-sd-card/
    Relocate dabao_v3c board, Library.pretty, gerbers, production, docs/pinout.
    Add .gitignore for fp-info-cache, KiCad backups, lock files.
    Remove nested .git from working copy so tree is tracked by main repo.
    Made-with: Cursor
2026-06-18 Clarify integrity checking for crates in README
    Updated README to clarify crate integrity checking.
2026-06-18 Hardware: add kicad-files-usb (no-SD dabao_v3c), refresh kicad-sd-card exports
    Add USB-only KiCad tree under kicad-files-usb with .gitignore excluding
    backups and fp-info-cache. Update kicad-sd-card PCB, PDF, previews, and gerbers.
    Made-with: Cursor
2026-06-18 Add crypto-verify tool link to README
    Added a link to the crypto-verify tool for testing.
2026-06-18 docs: document kicad-files-usb alongside kicad-sd-card in README
    Made-with: Cursor
2026-06-18 Add biometric crates, tests, fuzz target, threat model, and docs
    - biometric-api: CBOR wire format, Ed25519 match validation, trait drivers
    - biometric-vault: template encrypt/decrypt, session HMAC helpers
    - biometric-fingervein and biometric-sweet: host stubs and test-hal mocks
    - security-tests: dudect harnesses for biometric paths
    - fuzz: biometric_dispatch target; xtask aliases and test-all pipeline
    - Docs: BIOMETRIC_TESTING, DEVICE_GUIDE, FINGERVEIN_DEVICE, SWEET_PLATFORM,
2026-06-18 Add future expansion areas and Rust crates documentation
    This document outlines potential future use cases for the Galdralag firmware and identifies suitable Rust crates for implementation. It includes sections on password vaults, SSH authentication, email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
2026-06-18 docs: PAD ISO 30107-3, CandyFV/ESP32-CAM benchmarks, test patterns
    - Require ISO/IEC 30107-3 PAD methodology before deployment claims
    - Benchmark matching against CandyFV and ESP32-CAM paper datasets
    - Note Rust tests follow test-hal / dudect / cargo-fuzz workspace pattern
    Made-with: Cursor
2026-06-18 docs: align future-todo with codebase; README scope (no FIDO2/TOTP/HID)
    - future-todo: clarify ephemeral-session vs device ECDH, host-orchestrated
    Shamir, decoy storage as design-only, audit table caveat
    - README: add What this firmware is (and is not); link future-todo exclusions
    Made-with: Cursor
2026-06-18 Document LUKS Volume Unlock via Token feature
    Add documentation for LUKS Volume Unlock via Token feature, including design rationale, key unwrapping paths, and integration instructions.
2026-06-18 Fix HTML entities and improve README clarity
    Updated README.md to correct HTML entity references and improve clarity.
2026-06-18 Add NFC antenna selection and design documentation
    Document NFC antenna selection, matching network design, and PN532 integration details for the Dabao USB security token.
2026-06-18 Add CCID OpenPGP support and provisioning logic
    Implement CCID OpenPGP support and first-boot PIN provisioning in services/usb-bao1x. This includes new files for CCID initialization and provisioning logic, along with minimal edits to existing file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
2026-06-18 Update NFC antenna documentation with power details
    Clarified power requirements and NFC operation modes for the Baochip-1x platform. Updated connection summary for PN532.
2026-06-18 updated files

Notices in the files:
README.md:
GNU General Public License v3.0 — see [LICENSE](LICENSE).
The [Contribute](https://sequoia-pgp.org/contribute/) page describes licensing (LGPL 2.0 or later for most projects), the Developer Certificate of Origin, and that **larger commercial features** may require prior agreement and long-term maintenance arrangements — read that page before investing sign
- **Fully open stack** — CERN-OHL-W-2.0 RTL, open schematics, reproducible
